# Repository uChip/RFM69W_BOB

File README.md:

# Breakout PCB for RFM69W radio transceiver 

___

Eagle CAD PCB designs for radio transceiver breakout board. 
Converts the RFM69W radio transceiver from SMT to 0.1" breadboard format.  This board uses the same pinout as the [JeeLabs RFM12B breakout board] (http://www.digitalsmarties.net/products/rfm12b-board) for compatibility.  Note you cannot solder the RFM12B or the RFM69CW modules to this board.  Use an RFM69W or RFM69HW module instead.

See the following link for Arduino drivers for the RFM69W  
  * https://github.com/LowPowerLab/RFM69

A modified version of the RFM69 drivers that allows interchange between RFM69s and RFM12Bs is available in my github (forked from https://github.com/aanon4/RFM69).

Hookup of the breakout board to 5V Arduino SPI connection.  All board components populated.  Solder-jumpers left open.  

	Arduino			RFM69W BOB  
	  5V	-->		  5V  
	  GND	<-->	  GND  
	  D11	-->		  SDI  
	  D12	<--		  SDO  
	  D13	-->		  SCK  
	  D10	-->		  SEL  
	  D2	<--		  IRQ  
	  		<--		  3V3  
 
Hookup of the breakout board to 3.3V Arduino SPI connection.  On PCB populate only radio module, antenna, C2 and C4.  Short the pads on the solder-jumpers.  

	Arduino			RFM69W BOB  
	  NC	 		  5V  
	  GND	<-->	  GND  
	  D11	-->		  SDI  
	  D12	<--		  SDO  
	  D13	-->		  SCK  
	  D10	-->		  SEL  
	  D2	<--		  IRQ  
 	  3.3V	-->		  3V3  

## Order PCBs  

You can order this PCB directly from OSH Park.  Click on the following link.  
  * Radio Breakout - http://oshpark.com/shared_projects/bJRprI06  

See Bill of Materials file in repo for parts list.  

## Status  
  * PCB layout has been tested to be functional.   

## File Formats  

Design files are in "CadSoft EAGLE PCB Design Software" .brd and .sch formats.  
A free version of the software can be downloaded from www.cadsoftusa.com.  

## Distribution License  

You may use this PCB design however you like but no liability is accepted.

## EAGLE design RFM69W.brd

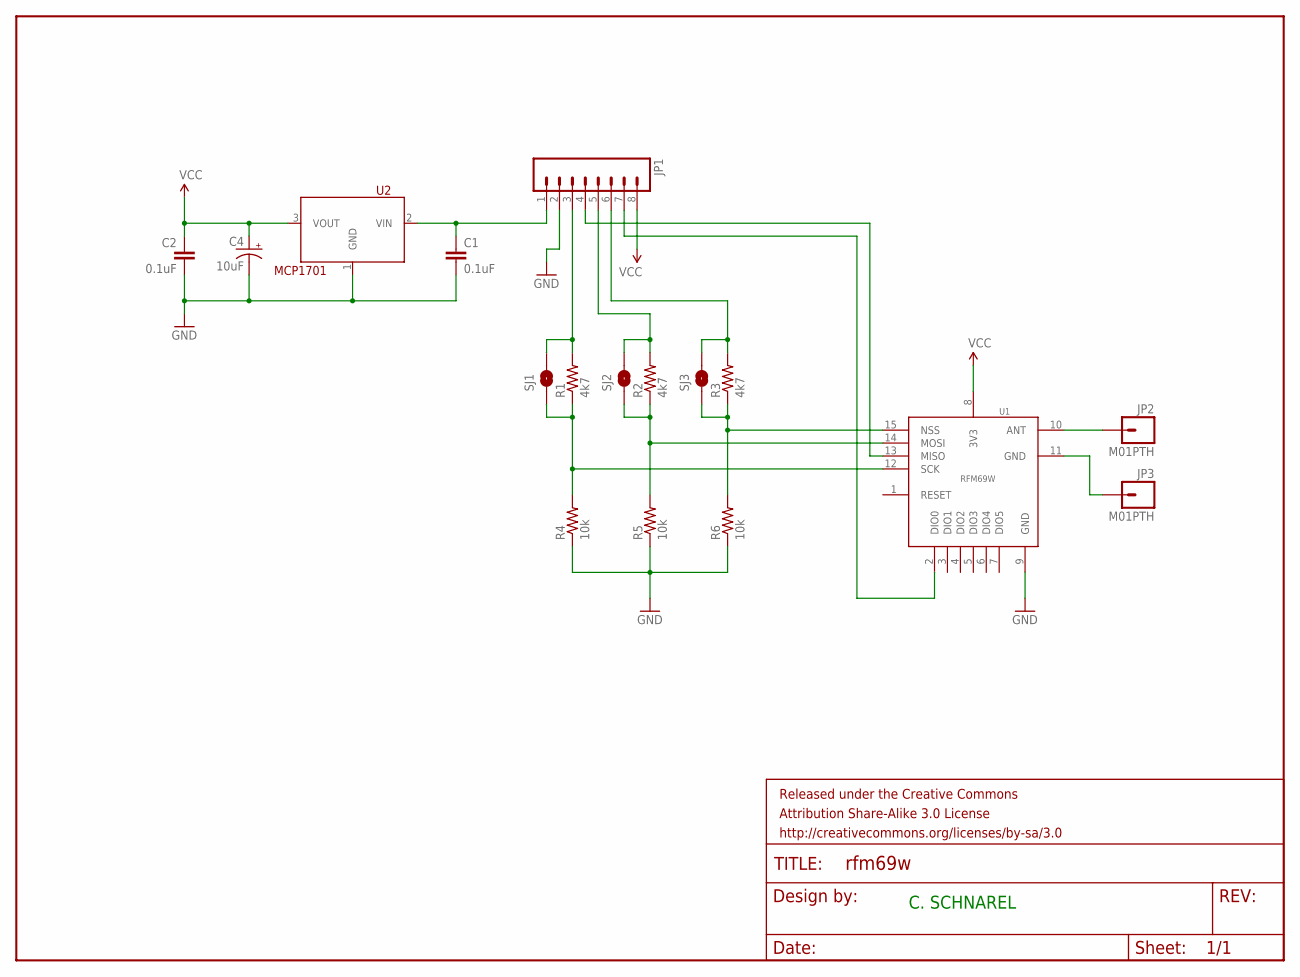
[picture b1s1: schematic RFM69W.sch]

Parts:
C1, C2: 0.1uF; 0805
C4: 10uF; 0805-POL
FRAME1: FRAME-LETTER; CREATIVE_COMMONS
JP1: M08LONGPADS; 1X08_LONGPADS
JP2, JP3: M01PTH; 1X01
R1, R2, R3: 4k7; 0805
R4, R5, R6: 10k; 0805
SJ1, SJ2, SJ3: SOLDERJUMPERNO; SJ_2S-NO
U1: RFM69W
U2: MCP1701; SOT-89

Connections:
GND: C1.2, C2.2, C4.2 (-), JP1.2, R4.1, R5.1, R6.1, U1.9 (GND), U2.1 (GND)
unnamed: R3.1, R6.2, SJ3.1, U1.15 (NSS)
unnamed: C1.1, JP1.1, U2.2 (VIN)
unnamed: JP1.4, U1.13 (MISO)
unnamed: JP1.7, U1.2 (DIO0)
unnamed: R2.1, R5.2, SJ2.1, U1.14 (MOSI)
unnamed: JP1.3, R1.2, SJ1.2
unnamed: JP1.5, R2.2, SJ2.2
unnamed: JP1.6, R3.2, SJ3.2
unnamed: R1.1, R4.2, SJ1.1, U1.12 (SCK)
unnamed: JP2.1, U1.10 (ANT)
unnamed: JP3.1, U1.11 (GND)
VCC: C2.1, C4.1 (+), JP1.8, U1.8 (3V3), U2.3 (VOUT)

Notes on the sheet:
C. SCHNAREL

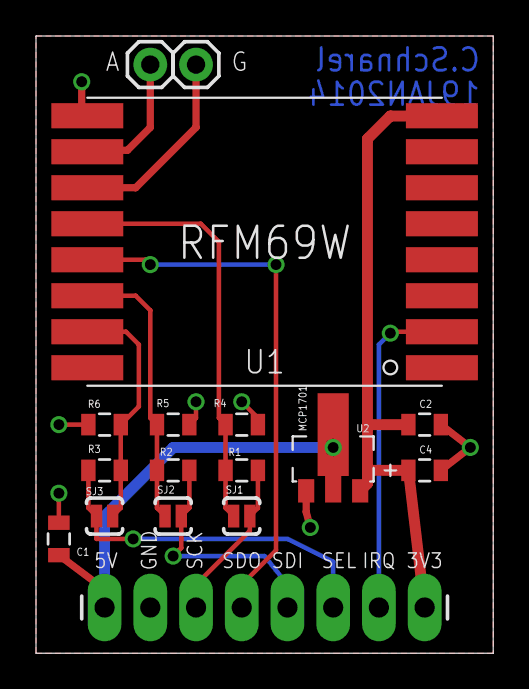
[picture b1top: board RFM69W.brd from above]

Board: 2 copper layers, 25.4 x 34.3 mm, 18 parts (0 on the bottom side), 13 nets.

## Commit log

2014-01-19 Initials Commit
    This is a breakout board (Eagle PCB design) for the HopeRF RFM69W radio
    transceiver
2014-01-19 Updated .gitignore and README
    Added README. Updated .gitignore to exclude Eagle backup files.
2014-01-19 Adding .png of board
2014-01-19 More README edits
2014-01-20 Add .png to README
2014-02-09 Updated README to confirm tested
    Also filled in value on bypass cap.
2014-02-09 Making png self referencial on github
    Change link in README to point to png in github repo.
2014-02-13 Added BOM file
2014-02-13 Updated README to reference BOM file
2014-02-27 Updating docs with new picture of working board.
2014-02-27 Doc formatting update
2014-02-28 More README.md updates
2014-03-02 Updating picture & README
    Image was wrong board. Changing to the right one.
2014-03-02 Corrected error in BOM
2015-03-02 Fix broken links in README

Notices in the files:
parts and their libraries:
SparkFun-Aesthetics: Licensing: CC v3.0 Share-Alike You are welcome to use this library for commercial purposes.
SparkFun-Aesthetics: Released under the Creative Commons Attribution Share-Alike 3.0 License
SparkFun-Aesthetics: http://creativecommons.org/licenses/by-sa/3.0
